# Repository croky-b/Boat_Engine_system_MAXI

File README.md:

# This is an Arduino RC engine sound & light & Servo controller for ESP32
Adaptation du projet de :https://github.com/TheDIYGuy999/Rc_Engine_Sound_ESP32
pour une utilisation "bateau" 

## Eratta : R29 = 10K 

## Version :
### version 5.7:
fonction special led 
multiswitch 
les fichiers des multiswitch arriveron bientot
### version 5.5:
- Integration des séquences 
### version 5.3:
- Bug sur VOSPER sound fixed 
### version 5.2:
- 
### Version 5.1:
- Configuration par HTML
### Version 5.0:
-

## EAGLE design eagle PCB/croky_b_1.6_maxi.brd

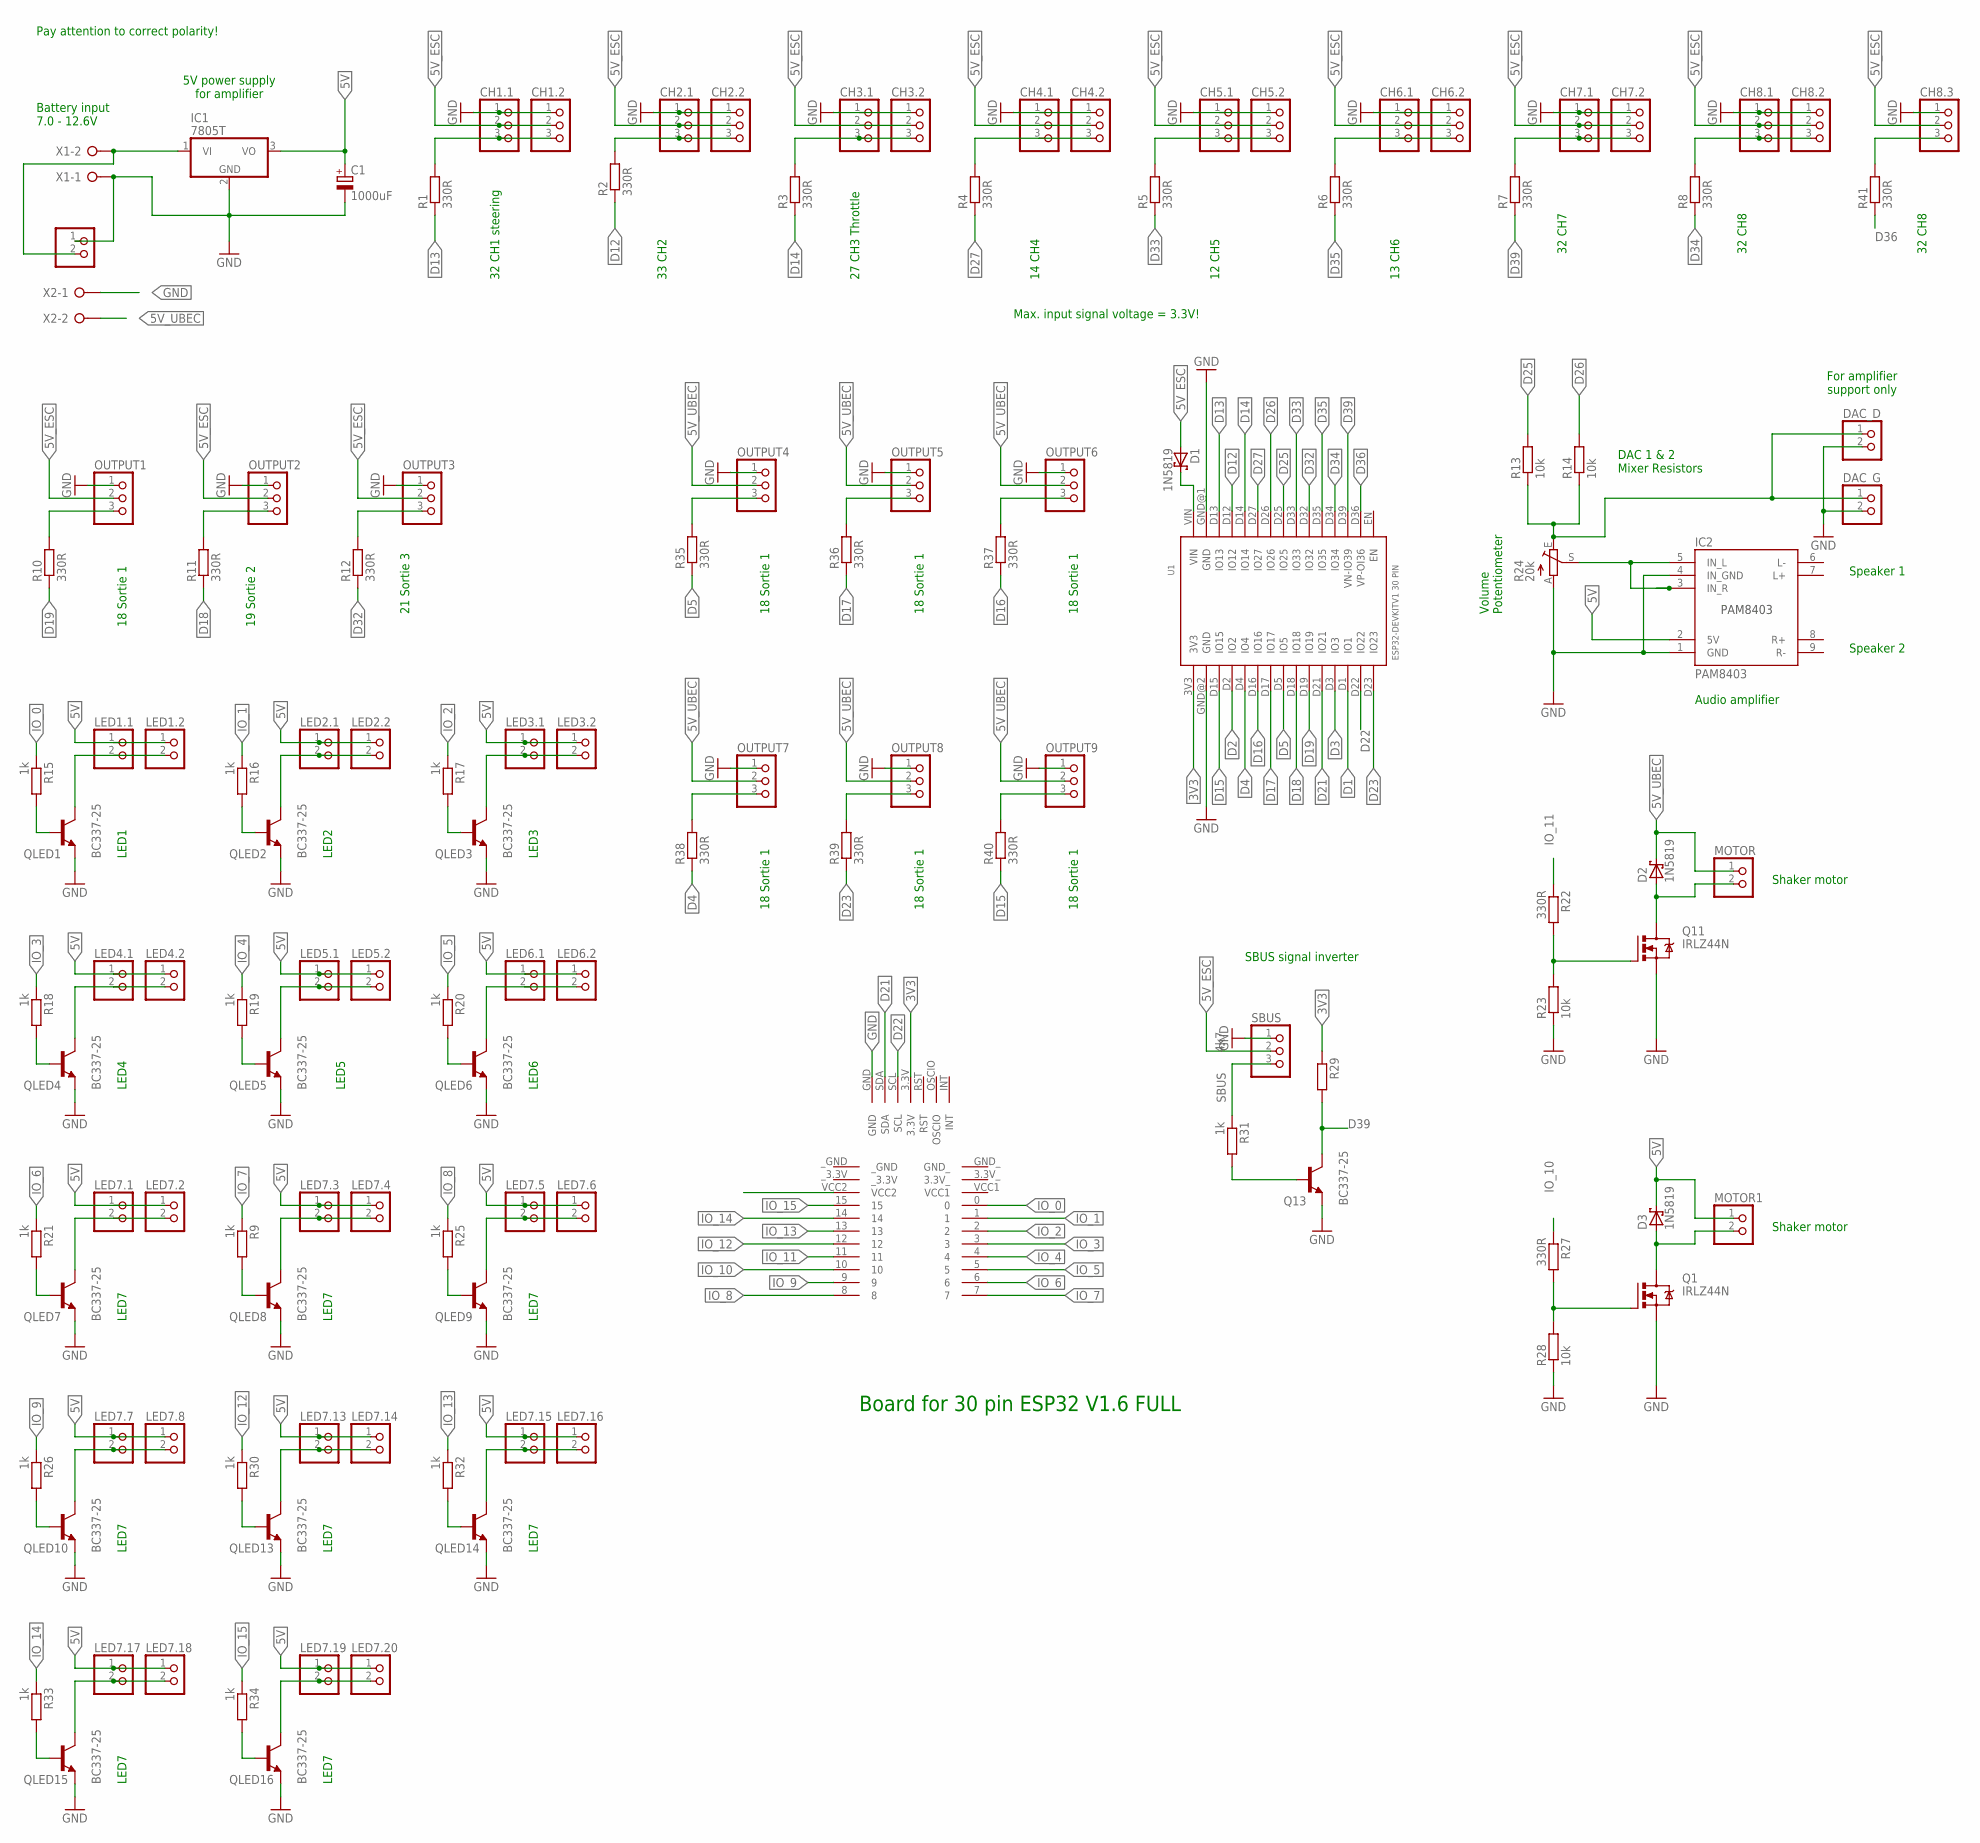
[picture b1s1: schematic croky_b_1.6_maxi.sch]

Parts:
C1: 1000uF; E5-10,5
CH1.1, CH1.2, CH2.1, CH2.2, CH3.1, CH3.2, CH4.1, CH4.2, CH5.1, CH5.2, CH6.1, CH6.2, CH7.1, CH7.2, CH8.1, CH8.2, CH8.3: PINHD-1X3; 1X03
D1, D2, D3: 1N5819; DO35-7
DAC_D: PINHD-1X2; 1X02
DAC_G: PINHD-1X2; 1X02
IC1: 7805T; TO220H
IC2: PAM8403
LED1.1, LED1.2, LED2.1, LED2.2, LED3.1, LED3.2, LED4.1, LED4.2, LED5.1, LED5.2, LED6.1, LED6.2, LED7.1, LED7.2, LED7.3, LED7.4, LED7.5, LED7.6, LED7.7, LED7.8, LED7.13, LED7.14, LED7.15, LED7.16, LED7.17, LED7.18, LED7.19, LED7.20: PINHD-1X2; 1X02
MOTOR, MOTOR1, MOTOR2: PINHD-1X2; 1X02
OUTPUT1, OUTPUT2, OUTPUT3, OUTPUT4, OUTPUT5, OUTPUT6, OUTPUT7, OUTPUT8, OUTPUT9: PINHD-1X3; 1X03
Q1, Q11: IRLZ44N; TO220BV
Q13: BC337-25; TO92
QLED1, QLED2, QLED3, QLED4, QLED5, QLED6, QLED7, QLED8, QLED9, QLED10, QLED13, QLED14, QLED15, QLED16: BC337-25; TO92
R1, R2, R3, R4, R5, R6, R7, R8, R10, R11, R12, R22, R27, R35, R36, R37, R38, R39, R40, R41: 330R; 0207/2V
R9, R15, R16, R17, R18, R19, R20, R21, R25, R26, R30, R31, R32, R33, R34: 1k; 0207/2V
R13, R14: 10k; 0207/10
R23, R28: 10k; 0207/2V
R24: 20k; S64W
R29: 4k7; 0207/2V
SBUS: PINHD-1X3; 1X03
U1: ESP32DEVKITV1; ESP32-DEVKITV1
U$1: TEST
X1, X2: W237-02P; W237-132

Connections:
3V3: R29.1, U1.3V3, U$1.3.3V
5V: C1.+, D3.C, IC1.3 (VO), IC2.2 (5V), LED1.1.1, LED1.2.1, LED2.1.1, LED2.2.1, LED3.1.1, LED3.2.1, LED4.1.1, LED4.2.1, LED5.1.1, LED5.2.1, LED6.1.1, LED6.2.1, LED7.1.1, LED7.2.1, LED7.3.1, LED7.4.1, LED7.5.1, LED7.6.1, LED7.7.1, LED7.8.1, LED7.13.1, LED7.14.1, LED7.15.1, LED7.16.1, LED7.17.1, LED7.18.1, LED7.19.1, LED7.20.1, MOTOR1.1
5V_ESC: CH1.1.2, CH1.2.2, CH2.1.2, CH2.2.2, CH3.1.2, CH3.2.2, CH4.1.2, CH4.2.2, CH5.1.2, CH5.2.2, CH6.1.2, CH6.2.2, CH7.1.2, CH7.2.2, CH8.1.2, CH8.2.2, CH8.3.2, D1.A, OUTPUT1.2, OUTPUT2.2, OUTPUT3.2, SBUS.2
5V_UBEC: D2.C, MOTOR.1, OUTPUT4.2, OUTPUT5.2, OUTPUT6.2, OUTPUT7.2, OUTPUT8.2, OUTPUT9.2, X2.2
-: LED2.1.2, LED2.2.2, QLED2.3 (C)
--: LED3.1.2, LED3.2.2, QLED3.3 (C)
BAT+: IC1.1 (VI), MOTOR2.2, X1.2
D1: U1.D1 (IO1)
D2: U1.D2 (IO2)
D3: U1.D3 (IO3)
D4: R38.1, U1.D4 (IO4)
D5: R35.1, U1.D5 (IO5)
D12: R2.1, U1.D12 (IO12)
D13: R1.1, U1.D13 (IO13)
D14: R3.1, U1.D14 (IO14)
D15: R40.1, U1.D15 (IO15)
D16: R37.1, U1.D16 (IO16)
D17: R36.1, U1.D17 (IO17)
D18: R11.1, U1.D18 (IO18)
D19: R10.1, U1.D19 (IO19)
D21: U1.D21 (IO21), U$1.SDA
D22: U1.D22 (IO22), U$1.SCL
D23: R39.1, U1.D23 (IO23)
D25: R13.2, U1.D25 (IO25)
D26: R14.2, U1.D26 (IO26)
D27: R4.1, U1.D27 (IO27)
D32: R12.1, U1.D32 (IO32)
D33: R5.1, U1.D33 (IO33)
D34: R8.1, U1.D34 (IO34)
D35: R6.1, U1.D35 (IO35)
D36: R41.1, U1.D36 (VP-OI36)
D39: Q13.3 (C), R7.1, R29.2, U1.D39 (VN-IO39)
GND: C1.-, CH1.1.1, CH1.2.1, CH2.1.1, CH2.2.1, CH3.1.1, CH3.2.1, CH4.1.1, CH4.2.1, CH5.1.1, CH5.2.1, CH6.1.1, CH6.2.1, CH7.1.1, CH7.2.1, CH8.1.1, CH8.2.1, CH8.3.1, DAC_D.2, DAC_G.2, IC1.2 (GND), IC2.1 (GND), IC2.4 (IN_GND), MOTOR2.1, OUTPUT1.1, OUTPUT2.1, OUTPUT3.1, OUTPUT4.1, OUTPUT5.1, OUTPUT6.1, OUTPUT7.1, OUTPUT8.1, OUTPUT9.1, Q1.S, Q11.S, Q13.1 (E), QLED1.1 (E), QLED2.1 (E), QLED3.1 (E), QLED4.1 (E), QLED5.1 (E), QLED6.1 (E), QLED7.1 (E), QLED8.1 (E), QLED9.1 (E), QLED10.1 (E), QLED13.1 (E), QLED14.1 (E), QLED15.1 (E), QLED16.1 (E), R23.1, R24.A, R28.1, SBUS.1, U1.GND@1 (GND), U1.GND@2 (GND), U$1.GND, X1.1, X2.1
IO_0: R15.1, U$1.0
IO_1: R16.1, U$1.1
IO_2: R17.1, U$1.2
IO_3: R18.1, U$1.3
IO_4: R19.1, U$1.4
IO_5: R20.1, U$1.5
IO_6: R21.1, U$1.6
IO_7: R9.1, U$1.7
IO_8: R25.1, U$1.8
IO_9: R26.1, U$1.9
IO_10: R27.1, U$1.10
IO_11: R22.1, U$1.11
IO_12: R30.1, U$1.12
IO_13: R32.1, U$1.13
IO_14: R33.1, U$1.14
IO_15: R34.1, U$1.15
unnamed: IC2.3 (IN_R), IC2.5 (IN_L), R24.S
unnamed: CH6.1.3, CH6.2.3, R6.2
unnamed: Q11.G, R22.2, R23.2
unnamed: CH5.1.3, CH5.2.3, R5.2
unnamed: CH4.1.3, CH4.2.3, R4.2
unnamed: CH7.1.3, CH7.2.3, R7.2
unnamed: CH3.1.3, CH3.2.3, R3.2
unnamed: D1.C, U1.VIN
unnamed: CH1.1.3, CH1.2.3, R1.2
unnamed: OUTPUT1.3, R10.2
unnamed: OUTPUT2.3, R11.2
unnamed: OUTPUT3.3, R12.2
unnamed: CH2.1.3, CH2.2.3, R2.2
unnamed: D2.A, MOTOR.2, Q11.D
unnamed: QLED1.2 (B), R15.2
unnamed: QLED6.2 (B), R20.2
unnamed: LED1.1.2, LED1.2.2, QLED1.3 (C)
unnamed: LED6.1.2, LED6.2.2, QLED6.3 (C)
unnamed: DAC_D.1, DAC_G.1, R13.1, R14.1, R24.E
unnamed: QLED8.2 (B), R9.2
unnamed: QLED3.2 (B), R17.2
unnamed: LED7.3.2, LED7.4.2, QLED8.3 (C)
unnamed: QLED2.2 (B), R16.2
unnamed: QLED9.2 (B), R25.2
unnamed: LED7.5.2, LED7.6.2, QLED9.3 (C)
unnamed: QLED7.2 (B), R21.2
unnamed: LED7.1.2, LED7.2.2, QLED7.3 (C)
unnamed: QLED4.2 (B), R18.2
unnamed: LED4.1.2, LED4.2.2, QLED4.3 (C)
unnamed: QLED10.2 (B), R26.2
unnamed: LED7.7.2, LED7.8.2, QLED10.3 (C)
unnamed: Q1.G, R27.2, R28.2
unnamed: D3.A, MOTOR1.2, Q1.D
unnamed: QLED5.2 (B), R19.2
unnamed: LED5.1.2, LED5.2.2, QLED5.3 (C)
unnamed: Q13.2 (B), R31.2
unnamed: CH8.3.3, R41.2
unnamed: QLED13.2 (B), R30.2
unnamed: CH8.1.3, CH8.2.3, R8.2
unnamed: LED7.13.2, LED7.14.2, QLED13.3 (C)
unnamed: QLED14.2 (B), R32.2
unnamed: LED7.15.2, LED7.16.2, QLED14.3 (C)
unnamed: QLED15.2 (B), R33.2
unnamed: LED7.17.2, LED7.18.2, QLED15.3 (C)
unnamed: QLED16.2 (B), R34.2
unnamed: LED7.19.2, LED7.20.2, QLED16.3 (C)
unnamed: OUTPUT4.3, R35.2
unnamed: OUTPUT5.3, R36.2
unnamed: OUTPUT6.3, R37.2
unnamed: OUTPUT7.3, R38.2
unnamed: OUTPUT8.3, R39.2
unnamed: OUTPUT9.3, R40.2
SBUS: R31.1, SBUS.3

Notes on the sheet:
Speaker 1
Speaker 2
13 CH6
12 CH5
14 CH4
27 CH3 Throttle
33 CH2
32 CH1 steering
18 Sortie 1
19 Sortie 2
21 Sortie 3
DAC 1 & 2 Mixer Resistors
Audio amplifier
Volume Potentiometer
5V power supply for amplifier
Battery input 7.0 - 12.6V
Board for 30 pin ESP32 V1.6 FULL
Shaker motor
LED1
LED6
LED3
LED2
LED7
LED4
LED5
For amplifier support only
Pay attention to correct polarity!
Max. input signal voltage = 3.3V!
32 CH7
32 CH8
SBUS signal inverter

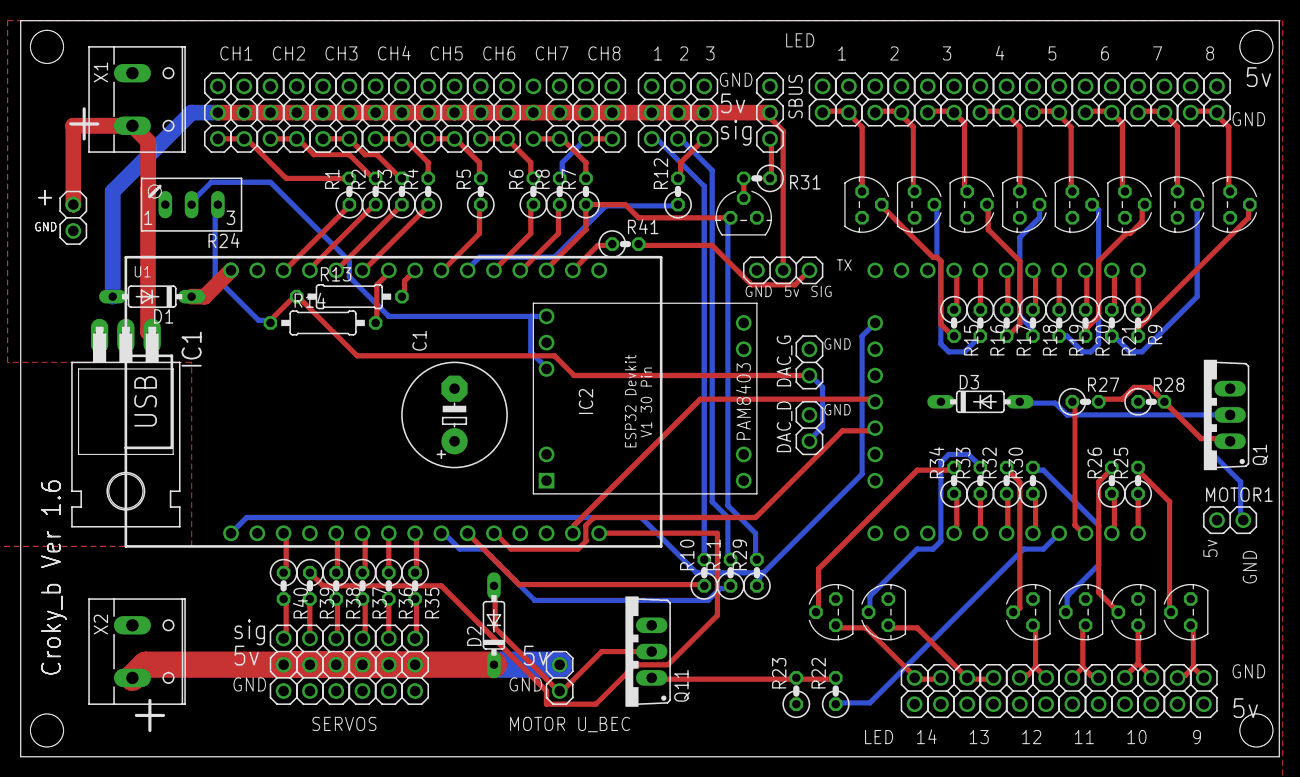
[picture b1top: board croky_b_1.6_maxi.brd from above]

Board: 2 copper layers, 121.6 x 71.1 mm, 128 parts (1 on the bottom side), 99 nets.

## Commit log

2020-11-27 Add files via upload
    Ver 5.2
    new Config
2021-02-04 Minor Bug
2022-03-25 Add files via upload
    bug in shortblast1 et longblast1 files
2022-10-18 Update Sound.ino
    bug with action 3
2022-10-18 Update Action.ino
    bug multiswitch action 8
